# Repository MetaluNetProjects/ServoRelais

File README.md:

# ServoRelais
Security ground-disconnector for GroupeF's drones

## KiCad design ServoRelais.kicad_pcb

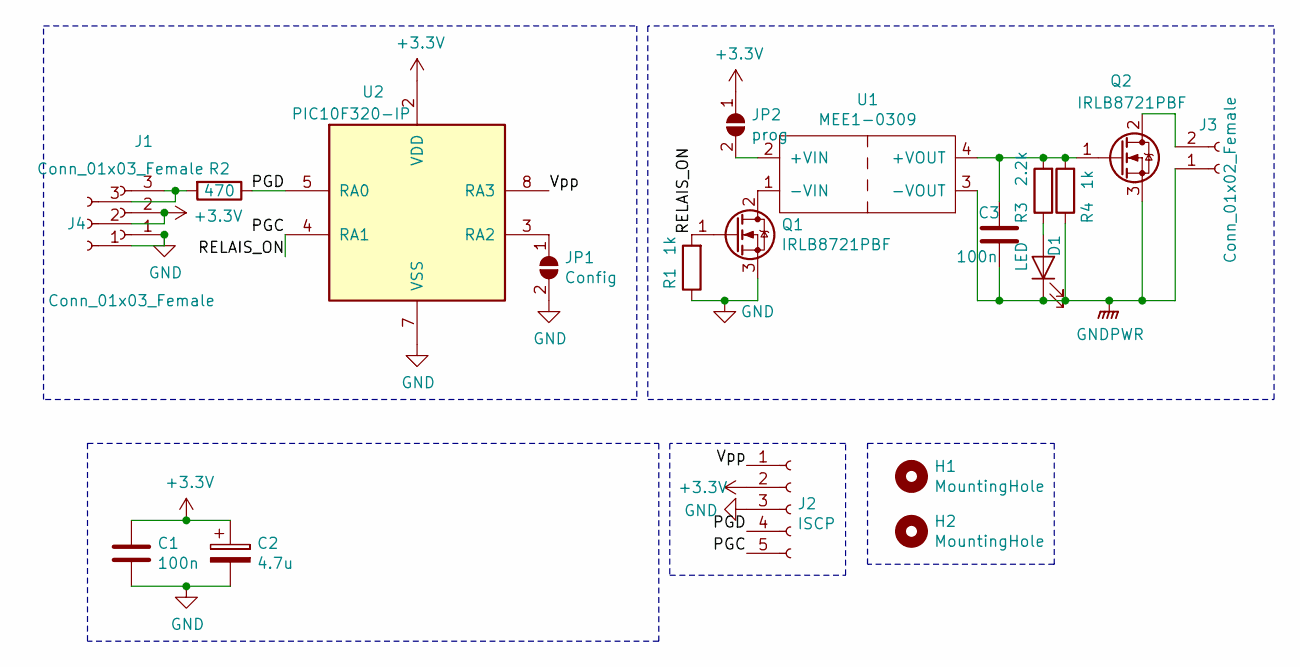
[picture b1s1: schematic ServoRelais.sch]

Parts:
C1, C3: 100n; C_Rect_L4.6mm_W2.0mm_P2.50mm_MKS02_FKP02
C2: 4.7u; CP_Radial_D4.0mm_P1.50mm
D1: LED; LED_D3.0mm
H1, H2: MountingHole; MountingHole_3.2mm_M3
J1, J4: Conn_01x03_Female; Molex_KK-6410-03_03x2.54mm_Straight
J2: ISCP; Pin_Header_Straight_1x05_Pitch2.54mm
J3: Conn_01x02_Female; TerminalBlock_bornier-2_P5.08mm
JP1: Config; GS2
JP2: prog; GS2
Q1, Q2: IRLB8721PBF; TO-252-2
R1, R4: 1k; R_Axial_DIN0207_L6.3mm_D2.5mm_P7.62mm_Horizontal
R2: 470; R_Axial_DIN0207_L6.3mm_D2.5mm_P7.62mm_Horizontal
R3: 2.2k; R_Axial_DIN0207_L6.3mm_D2.5mm_P7.62mm_Horizontal
U1: MEE1-0309; DCDC-Conv_muRata_CRE1xxxxxxSC
U2: PIC10F320-IP; DIP-8_W7.62mm_LongPads

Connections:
+3V3: C1.1, C2.1, J1.2, J2.2, J4.2, JP2.1 (A), U2.2 (VDD)
/PGC: J2.5, Q1.1 (G), R1.2, U2.4 (RA1)
/PGD: J2.4, R2.1, U2.5 (RA0)
/Vpp: J2.1, U2.8 (RA3)
GND: C1.2, C2.2, J1.1, J2.3, J4.1, JP1.2 (B), Q1.3 (S), R1.1, U2.7 (VSS)
GNDPWR: C3.2, D1.1 (K), J3.1, Q2.3 (S), R4.1, U1.3 (-VOUT)
unnamed: C3.1, Q2.1 (G), R3.2, R4.2, U1.4 (+VOUT)
unnamed: D1.2 (A), R3.1
unnamed: J1.3, J4.3, R2.2
unnamed: J3.2, Q2.2 (D)
unnamed: JP1.1 (A), U2.3 (RA2)
unnamed: JP2.2 (B), U1.2 (+VIN)
unnamed: Q1.2 (D), U1.1 (-VIN)

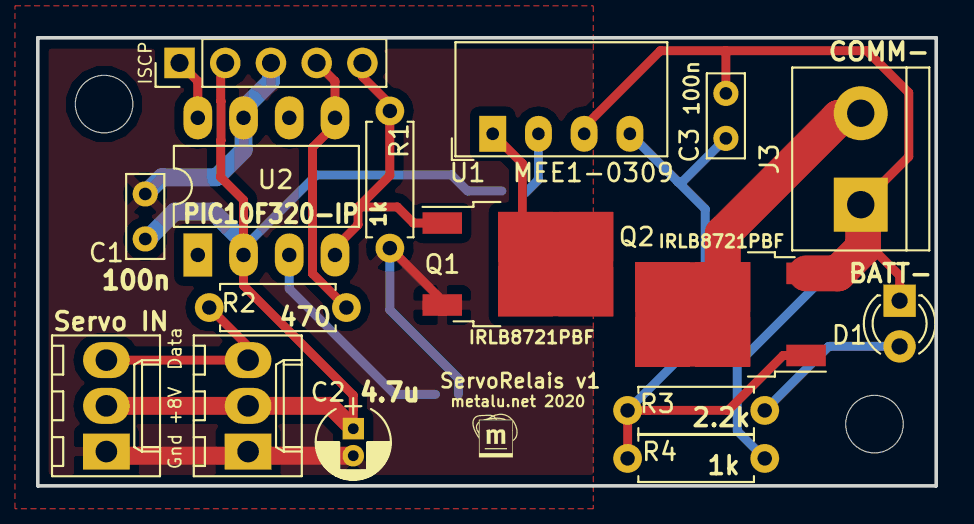
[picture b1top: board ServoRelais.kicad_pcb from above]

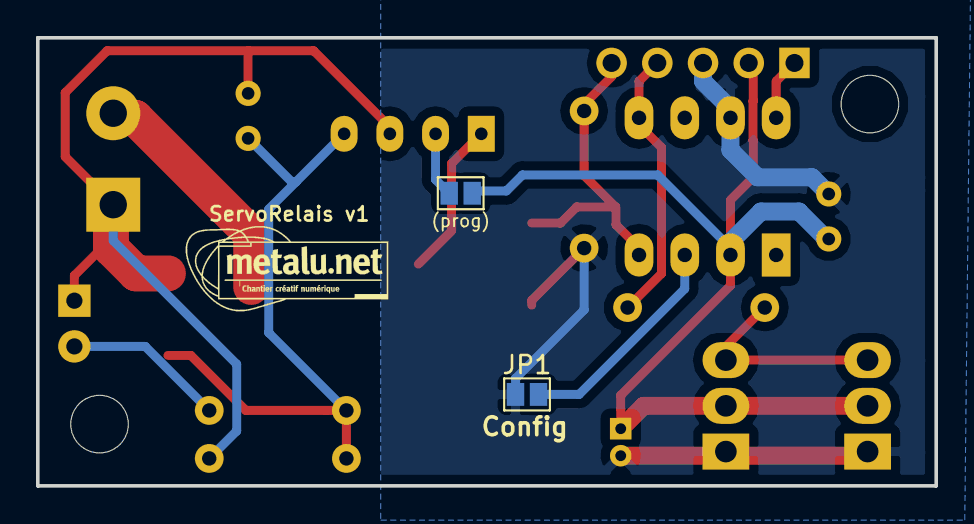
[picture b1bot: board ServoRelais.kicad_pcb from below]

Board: 2 copper layers, 49.9 x 24.9 mm, 20 parts (2 on the bottom side), 13 nets.

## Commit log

2020-11-12 write firmware (untested)
2020-11-16 finish PCB, using ASSR-1611 as a 5A circuit breaker.
2020-11-16 firmware: active pullups
2020-11-17 use a 3v->9V dc-dc converter. version 1.3
2020-11-18 debug firmware (mainly disable analog inputs)
2020-11-18 add test Fraise servo emitter
2020-11-18 PCB: add solder-switch to disable powering the DC-DC converter (else programming of the PIC fails because of power loss)
2021-01-19 wait 10 seconds debefore switching on
2021-01-19 PCB 1.2: add 25Vmax->3V3 regulator
